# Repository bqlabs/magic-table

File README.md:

Magic Table
-------------

HBot-based 2D CNC machine for different applications.

# Repository Structure
(Check out each folder's README file for more info on subfolders)

 * /
   * /doc -> Documentation of FESTO hardware parts and tests performed with the machine
   * /firmware ->  Firmware for different embedded devices that that work with the Magic Table
   * /hardware -> Both 3D printable mechanical parts and PCBs for accesories.
   * /software -> Programs to control the Magic Table and use it in different applications.

# Applications developed

## LightPainting
Draw 2D shapes with an RGB light.

## Magic Table
Control different pieces and figures with an electromagnet.

# Credits

 * Author: [David Estevez Fernandez](https://github.com/David-Estevez)

# License

This machine is licensed under a [Creative Commons Attribution-ShareAlike 4.0 International License](http://creativecommons.org/licenses/by-sa/4.0/). Please read the LICENSE files for more details.

Esta maquina tiene una licencia [Creative Commons Attribution-ShareAlike 4.0 International License](http://creativecommons.org/licenses/by-sa/4.0/). Por favor, lea los ficheros LICENSE para más detalles

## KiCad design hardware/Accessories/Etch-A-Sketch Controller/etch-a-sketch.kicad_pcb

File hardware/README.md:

# Hardware
## Accessories
PCB designs for different accesories, like the etch-a-sketcher or the electromagnet controller board.

## CoreXY Essencials
Set of 3D-printable parts to set the most basic configurations of the magic table

## Light Painting
Set of 3D-printable parts to attach the LED for light paiting applications

## Magic Table
Set of 3D-printable parts to attach the electromagnet and the top cover for the "magic table" applications.

This folder also includes the pieces and backgrounds for each of the "magic table" applications.

## Utils
Different 3D-printable parts to attach accessories such as a webcam to the magic table.

# Z Axis
Set of 3D-printable parts to add a (proof of concept) Z axis.

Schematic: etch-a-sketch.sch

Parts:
BOARD1: BOARD_TEENSY_3.1
C1, C2, C3, C4: C
D1, D3: GREEN
D2, D4: RED
EN1, EN2: MISC_ENCODER_5_PINS
R1, R2, R3, R4, R5, R6, R7, R8, R9, R10, R11, R12: R
SW1, SW2, SW3, SW4: DPST

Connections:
/D0: BOARD1.2, C2.1, R4.2
/D1: BOARD1.3, C1.1, R3.2
/D2: BOARD1.4, EN1.4
/D9: BOARD1.11, SW3.3
/D10: BOARD1.12, SW1.3
/D11: BOARD1.13, D3.1 (A)
/D12: BOARD1.14, D1.1 (A)
/D14: BOARD1.16, D2.1 (A)
/D15: BOARD1.17, D4.1 (A)
/D16: BOARD1.18, SW2.3
/D17: BOARD1.19, SW4.3
/D21: BOARD1.23, EN2.4
/D22: BOARD1.24, C4.1, R8.2
/D23: BOARD1.25, C3.1, R7.2
GND: BOARD1.1, C1.2, C2.2, C3.2, C4.2, EN1.2, EN1.5, EN2.2, EN2.5, R9.2, R10.2, R11.2, R12.2, SW1.2, SW2.2, SW3.2, SW4.2
unnamed: D1.2 (K), R9.1
unnamed: D3.2 (K), R11.1
unnamed: D4.2 (K), R12.1
unnamed: D2.2 (K), R10.1
unnamed: EN1.3, R2.1, R4.1
unnamed: EN1.1, R1.1, R3.1
unnamed: EN2.3, R6.1, R8.1
unnamed: EN2.1, R5.1, R7.1
VCC: BOARD1.26, R1.2, R2.2, R5.2, R6.2

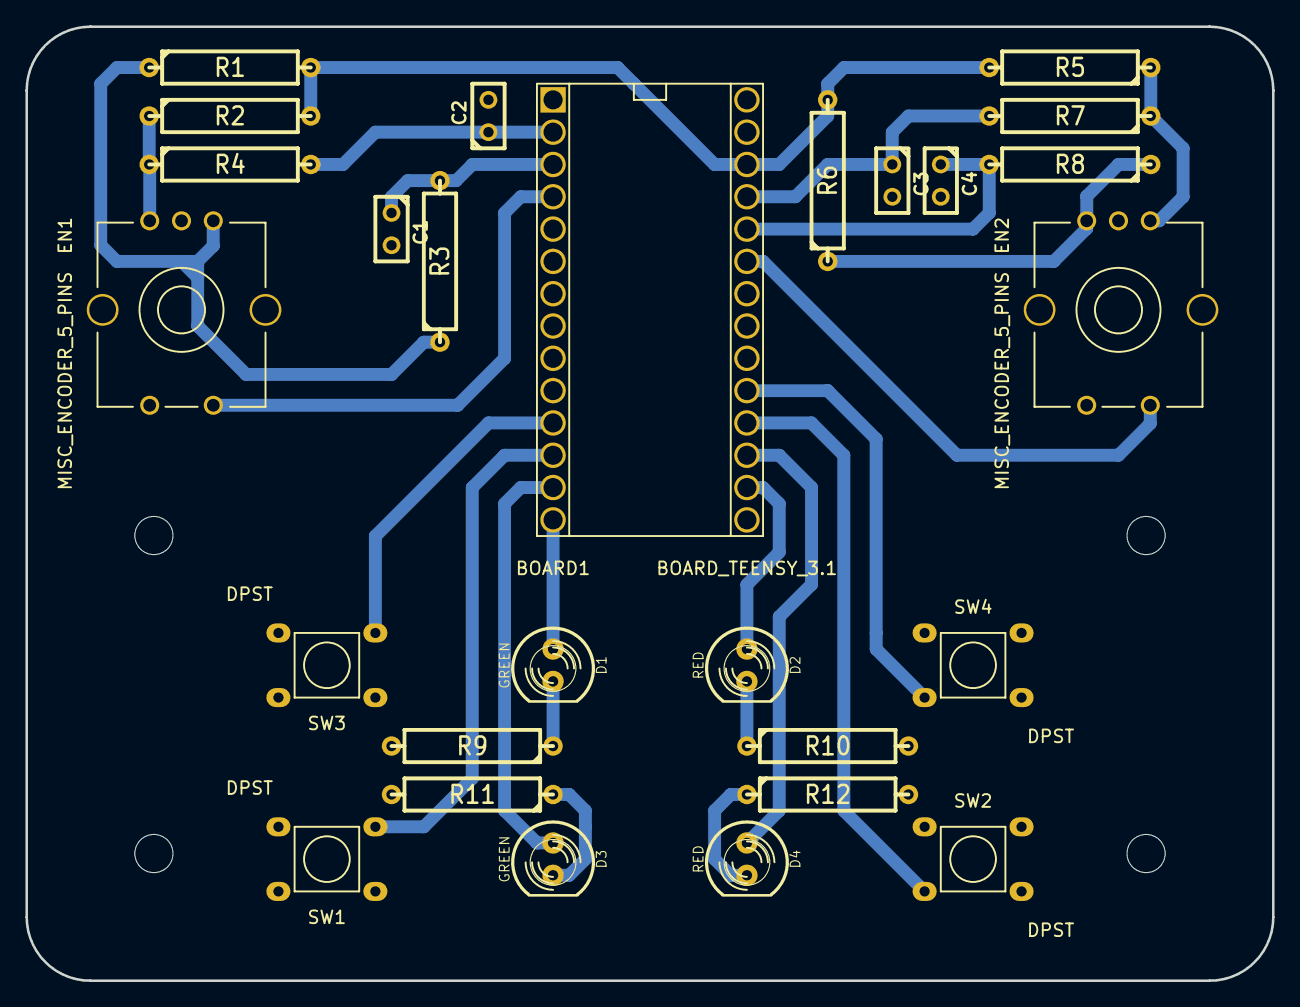
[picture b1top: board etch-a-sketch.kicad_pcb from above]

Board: 2 copper layers, 98.0 x 75.0 mm, 31 parts (0 on the bottom side), 24 nets.

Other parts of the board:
Mechanical_drill_3mm, Mechanical_drill_3mm#2, Mechanical_drill_3mm#3, Mechanical_drill_3mm#4: Mechanical_drill_3mm

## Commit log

2014-12-11 Initial commit.
2014-12-12 Added test for supports.
2014-12-12 Add all supports.
2014-12-12 Minor changes
2014-12-15 Added firsts steps of bottom left leg (upper part of the leg)
2014-12-15 Finished upper part of the bottom left leg
2014-12-16 Leg body (bottom left) sketch finished.
2014-12-19 Added both bottom legs.
2014-12-19 Modified tolerances of bottom legs
2014-12-22 Added motor leg top part
2014-12-22 Add screw head holes to leg top part.
2014-12-22 Motor support leg added.
2014-12-22 Add both motor legs.
2014-12-23 Add v2 motor support. Add base sketch.
2014-12-23 Add chamfered base.
2014-12-30 Correct "Motor Body Leg" part with the correct dimensions.
    Changes:
    - Add correct NEMA 17 model (47mm)
    - Update motor body leg part
    - Started to modify top part
2014-12-30 Fix Leg Motor Top part
    Changes:
    - Add extra holes to attach supports
2014-12-30 Update base position
2014-12-30 Completed remaining legs
2014-12-30 Start creating the endstop holder
2015-01-12 Base sketch of the endstop holder (now really)
2015-01-12 Endstop holder and leg top part finished
2015-02-02 Added Arduino holder.
2015-02-05 Arduino holder added and tested.
2015-02-09 Add stl files for the CoreXY basic functionality
2015-02-09 Add base file for laser cutting
2015-02-09 Start working on Ligh Painting code
    Add functions to reduce image dimensions and depth, prior to 'slicing'
2015-02-10 Add Instructions for CoreXY setup and Travel
2015-02-11 Add M8 threaded rod holder
2015-02-16 Add M8 threaded rod connectors
2015-02-16 Place RAMPS holder in correct position.
2015-02-19 Add code to simulate lightpainting
2015-02-24 Images for testing software
2015-02-24 Backup of some stl files in development
2015-02-24 Add M8 rod connectors for webcam structure
2015-02-24 Add function to change coordinate systems
2015-02-25 Basic led movement with CoreXY
2015-02-26 Add ImageIterator to traverse images row by row
2015-02-26 Added Iterators / Paint instructions
2015-03-02 Add CoreXY class to control CoreXY through serial port
2015-03-03 Add checking ok messages (not working yet)
2015-03-04 CoreXY python API is now working
2015-03-04 Add function to move CoreXY in pseudo-real time
2015-03-04 Comment debug message
2015-03-09 Add utils to convert gcode for lightpainting
2015-03-10 Create endstop holder for X axis (draft)
2015-03-10 Update example/test to move to a series of points
2015-03-13 Add firmware for caliper and control board
2015-03-13 Add mode1: cursor position control
2015-03-24 Add Marlin patch to support wait for GPIO
2015-03-24 Add instructions to patch
2015-03-24 Add documentation files with results
2015-03-24 Add support for different colors
2015-03-24 Solve bug (-1 is used for not found in string, not 1)
2015-03-24 Add tests for CoreXY connectivity
2015-03-24 Add function to send raw commands
2015-03-24 Add gitignore
2015-03-24 Add test controller just to keep track of it
2015-03-24 Controller no longer needed (now it is done from modified Marlin)
2015-03-25 Add kicad library as submodule
2015-03-25 Corrected issue with LED colors (BGR vs RGB)
2015-03-25 Correct turning direction
2015-03-25 Ignoring bak files
2015-03-25 Add schematic for etch-a-sketch accessory
2015-03-25 Add power flags
2015-03-26 Update kicad lib with push switch
2015-03-26 Add netlist and component association
2015-03-30 New footprints in kicad-library required
2015-03-30 Add pcb design
2015-03-30 Add encoder with gnd shield connection.
2015-03-30 Add version adapted to be manufatured in cyclone
2015-03-30 WebcamFeedback script is now standalone
2015-03-30 Add Lightpainting result images for documentation
2015-03-30 Move transform_image to Utils
2015-03-30 LightPainter is now standalone
2015-03-30 Move files to a folder for Lightpainter apps
2015-03-30 Fixed coordinate frame bug (as I changed the endstop position)
2015-03-31 Remake Y axis endstop holder
2015-03-31 Fix and place endstop holders
2015-03-31 Move files to more logical place
2015-03-31 Rename part
2015-03-31 Add manufacturing file for base
2015-03-31 Move M8 connectors to Utils
2015-03-31 Move files to more coherent places
2015-04-15 Convert Lightnizer to standalone app
2015-05-11 Add electromagnet toolhead
2015-05-13 Add electromagnet holder (single and dual)
2015-05-14 Add schematic for electromagnet controller board
2015-05-14 Remove versioning outside CVS
2015-06-02 Add qtcreator user files to gitignore
2015-06-02 Add .fcstd1 files to gitignore
2015-06-02 Add files for image stitching when using the microscope scanner
2015-06-02 Start working on OpenCV features with python
2015-06-03 Concepts for Z-axis
2015-06-17 Motor Holder almost finished (Top part)
2015-06-18 Lower holder part RC1 finished
2015-06-18 Motor attachment RC1
2015-07-09 Add Table holder Motor Leg and Endstop Y Leg
2015-07-13 Add Table holder for X endstop side
2015-07-13 Add assembly elements to magic table assembly
2015-07-14 Add mode0: scroll control
2015-07-14 Add acrylic surface to magic table
2015-07-15 Add Acrylic Table
2015-07-15 Add Acrylic Table to Assembly
2015-07-15 Add modified attachment
2015-07-17 Add M6x50 screw model
2015-07-17 Update top hole in Table Holder Endstop X
2015-07-17 Update top hole in Table Holder Endstop Y
2015-07-17 Modify Attachments to fit acrylic
2015-07-17 Modify top hole in Table Holder Base for Motor Legs
2015-07-17 Add all elements to assembly
2015-07-21 Add test server in CherryPy
2015-07-24 Modify Endstop holder Y axis wing height
2015-07-24 Add stl files to repository, clean repo
2015-07-24 Add files for knob
2015-07-24 Add Space Explorer files
2015-07-27 Add Ouija App files
2015-07-27 Add objects for Space Explorer app
2015-08-18 Basic Python module to control CoreXY
2015-08-18 Add controller for electromagnet toolhead
2015-08-19 Add GUI for CoreXY Controller
2015-08-19 Rename GUI label
2015-08-20 Add support for keyboard and cleanup at closing
2015-08-21 Add GUI support for simple magnet toolhead
2015-08-25 Add position feedback to GUI
2015-08-25 Add loading calibration files support
2015-08-25 Define interface for calibration
2015-08-26 Add functions to perform calibration
2015-08-27 Calibration widget almost working
2015-08-27 Solve ui loading problem
2015-08-27 Integration of calibration widget
2015-08-28 Add listeners for events ocurring in CoreXY
2015-08-28 Solve issues with listeners
2015-08-28 Add support for listening events from the CoreXY
2015-08-28 Add support for disconnecting on close window
2015-08-28 Refactor class to something with more sense
2015-08-28 Resize window after hiding widget
2015-08-28 Solve issue with cancelling the calibration task not affecting main window
2015-08-29 Finish Calibration GUI
2015-08-31 Refactor Calibration class
    Refactor done to convert the methods that extract the xml information static,
    so that they can be reused in the static method to load the calibration data.
2015-08-31 Add method to load calibration data from xml to a Python dict
2015-08-31 Rename file to CalibrationWidget.ui
2015-08-31 Add basic magic table controller
2015-08-31 Solve bug with toolhead position
2015-08-31 Update calibration file
2015-08-31 Add application: ouija
2015-08-31 MagicTableController configured from file
2015-09-01 Create app folder for ouija
2015-09-01 Add files for ouija app
2015-09-01 Add example config file
2015-09-01 Modify calibration example for less points
2015-09-01 Turn off magnets at end
2015-09-01 Add chessboard image file
2015-09-02 Add Trajectory load functions
2015-09-02 Implement path transformations
2015-09-03 Add getter for normalized path
2015-09-03 Add TrajectoryWidget
2015-09-04 Add files for app "WackyRaces"
2015-09-04 Trajectory Widget working
2015-09-04 Add start / abort interface
2015-09-04 Solve discritizing bug
2015-09-04 Test trajectory rendering ok
2015-09-08 Add support for trajectories in CoreXY (TrajectoryController)
2015-09-08 Solve bug raising exception
2015-09-09 Solve bug
2015-09-09 Add QFrame to button bar
2015-09-10 Add observable class to manage CoreXY events
2015-09-10 Refactor to use new CoreXYEventObservable interface
2015-09-11 Remove calibration file at root
2015-09-11 Add set_magnets_off to turn of all magents at once
2015-09-11 Add abstract class for Workspaces
2015-09-11 Fix minor bug in set_magnet_off
2015-09-11 Refactor Trajectory private methods to public
2015-09-11 Add new method to easily load different workspaces
2015-09-11 Pause workspace when another one is selected
2015-09-11 Add stop on request
2015-09-14 Add functions to stop thread.
2015-09-14 Changing workspace stops the movement
2015-09-14 Terminate thread when window is closed
2015-09-14 Debug mode off
2015-09-14 Add variable delay
2015-09-17 Add UI file for Chess App
2015-09-17 Add failing test for ChessEngine
2015-09-17 Add (empty) tests for coord transform and valid moves
2015-09-18 Add gcode generator mockup object
2015-09-18 Add mockup object for SimpleMagnet toolhead
2015-09-18 Add support for running mockup
2015-09-18 Fix small bug
2015-09-18 Generate gcodes from mockup objects with GUI
2015-09-28 Add app Chess
2015-09-29 First version of chessify
2015-09-29 Add more movements
2015-09-29 App Chess finished
2015-09-30 Add demo accesories (screen and controller holders)
2015-10-30 Add doc images
2015-10-30 Add README file
2015-10-30 Fix README
2015-11-02 Add firmware README
2015-11-02 Add README for hardware
2015-11-02 Add README for software
